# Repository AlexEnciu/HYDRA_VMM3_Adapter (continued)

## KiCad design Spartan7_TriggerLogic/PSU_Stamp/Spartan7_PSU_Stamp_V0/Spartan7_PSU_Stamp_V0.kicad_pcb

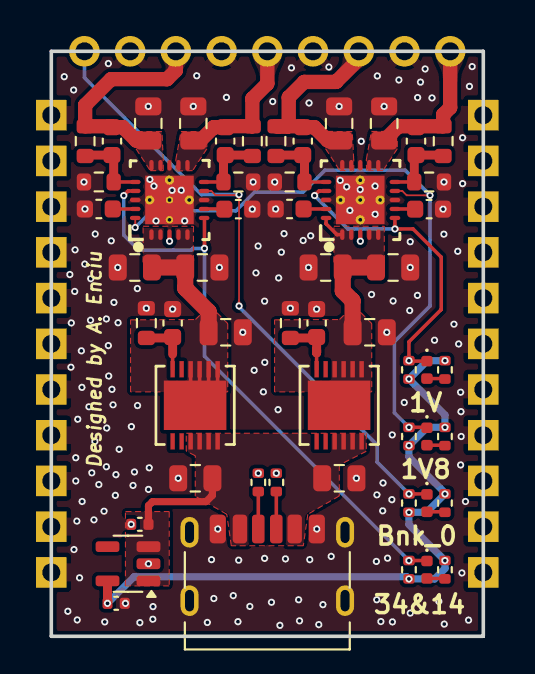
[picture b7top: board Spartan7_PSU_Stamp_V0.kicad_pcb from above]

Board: 4 copper layers, 24.0 x 32.5 mm, 77 parts (0 on the bottom side), 29 nets.

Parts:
C1, C3, C4, C6, C11, C12, C13, C14, C19, C20, C21, C22: 10uF; C_0805_2012Metric
C2, C5: 10p; C_0603_1608Metric
C7, C8, C9, C10: 100nF; C_0603_1608Metric
C15, C16, C17, C18: 10nF; C_0603_1608Metric
C23, C24: 1u; C_0402_1005Metric
D1, D2, D3, D4: 1V_ok; LED_0402_1005Metric
J1: USB4125-GF-A; USB_C_Receptacle_HRO_TYPE-C-31-M-17
J2: Castellated_holes; PinHeader_1x09_P2.54mm_Vertical
J7, J8, J9, J10, J11, J12, J13, J14, J15, J16, J17, J18, J19, J20, J21, J22, J23, J24, J25, J26, J27, J28: Conn_01x01_Pin; PinHeader_1x01_P2.54mm_Vertical
R1, R2: 40k; R_0603_1608Metric
R3, R4: R_3; R_0603_1608Metric
R5, R6: R_4; R_0603_1608Metric
R7, R9: R_1; R_0603_1608Metric
R8, R10: R_2; R_0603_1608Metric
R11, R14, R16, R18: 10k; R_0402_1005Metric
R12, R13, R15, R17: 680; R_0402_1005Metric
R19, R20: 5k1; R_0402_1005Metric
U1, U2: LT3081EDF-TRPBF; DFN-12_DF_LIT-M
U3, U4: TPS7A8801RTJT; RTJ0020D
U5: TPS7A2033; SOT-23-5

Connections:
+3V3: C24.1, R11.1, R12.1, R13.1, R14.1, R15.1, R16.1, R17.1, R18.1, U5.5 (Out)
+5V: C1.1, C4.1, C23.1, J1.A9 (VBUS), J1.B9 (VBUS), U1.9 (IN), U1.10 (IN), U1.11 (IN), U1.12 (IN), U2.9 (IN), U2.10 (IN), U2.11 (IN), U2.12 (IN), U5.1 (In), U5.3 (EN)
/2V5: C3.1, C11.1, C13.1, U1.1 (OUT), U1.2 (OUT), U1.3 (OUT), U1.4 (OUT), U1.13 (OUT), U3.1 (IN1), U3.2 (IN1), U3.4 (IN2), U3.5 (IN2), U3.20 (EN1)
/3V6: C6.1, C12.1, C14.1, U2.1 (OUT), U2.2 (OUT), U2.3 (OUT), U2.4 (OUT), U2.13 (OUT), U4.1 (IN1), U4.2 (IN1), U4.4 (IN2), U4.5 (IN2)
/DONE_0: D4.1 (K), J2.1, R18.2, U4.9 (PG2)
/PG_1V8_ok: D2.1 (K), R14.2, U3.9 (PG2), U4.20 (EN1)
/PG_1V_ok: D1.1 (K), R11.2, U3.6 (EN2), U3.17 (PG1)
/PG_3V3_14_ok: D3.1 (K), R16.2, U4.6 (EN2), U4.17 (PG1)
/V_Bank_14_3V3: C16.1, C22.1, J2.3, R9.1, U4.14 (OUT1), U4.15 (OUT1)
/V_Bank_34_3V3: C18.1, C20.1, J2.5, R4.1, U4.11 (OUT2), U4.12 (OUT2)
/V_aux_1V8: C17.1, C19.1, J2.9, R3.1, U3.11 (OUT2), U3.12 (OUT2)
/V_core_1V: C15.1, C21.1, J2.7, R7.1, U3.14 (OUT1), U3.15 (OUT1)
GND: C1.2, C2.2, C3.2, C4.2, C5.2, C6.2, C7.2, C8.2, C9.2, C10.2, C11.2, C12.2, C13.2, C14.2, C19.2, C20.2, C21.2, C22.2, C23.2, C24.2, J1.A12 (GND), J1.B12 (GND), J1.S1 (SHIELD), J2.2, J2.4, J2.6, J2.8, J7.1, J8.1, J9.1, J10.1, J11.1, J12.1, J13.1, J14.1, J15.1, J16.1, J17.1, J18.1, J19.1, J20.1, J21.1, J22.1, J23.1, J24.1, J25.1, J26.1, J27.1, J28.1, R1.2, R2.2, R5.2, R6.2, R8.2, R10.2, R19.2, R20.2, U3.3 (AGND), U3.8 (SS_CTRL2), U3.13 (AGND), U3.18 (SS_CTRL1), U3.21 (PAD), U4.3 (AGND), U4.8 (SS_CTRL2), U4.13 (AGND), U4.18 (SS_CTRL1), U4.21 (PAD), U5.2 (GND)
unnamed: D1.2 (A), R12.2
unnamed: D2.2 (A), R13.2
unnamed: D3.2 (A), R15.2
unnamed: D4.2 (A), R17.2
unnamed: J1.A5 (CC1), R20.1
unnamed: J1.B5 (CC2), R19.1
unnamed: C2.1, R1.1, U1.6 (SET)
unnamed: C5.1, R2.1, U2.6 (SET)
unnamed: C15.2, R7.2, R8.1, U3.16 (FB1)
unnamed: C17.2, R3.2, R5.1, U3.10 (FB2)
unnamed: C7.1, U3.19 (NR_SS1)
unnamed: C9.1, U3.7 (NR_SS2)
unnamed: C16.2, R9.2, R10.1, U4.16 (FB1)
unnamed: C18.2, R4.2, R6.1, U4.10 (FB2)
unnamed: C8.1, U4.19 (NR_SS1)
unnamed: C10.1, U4.7 (NR_SS2)

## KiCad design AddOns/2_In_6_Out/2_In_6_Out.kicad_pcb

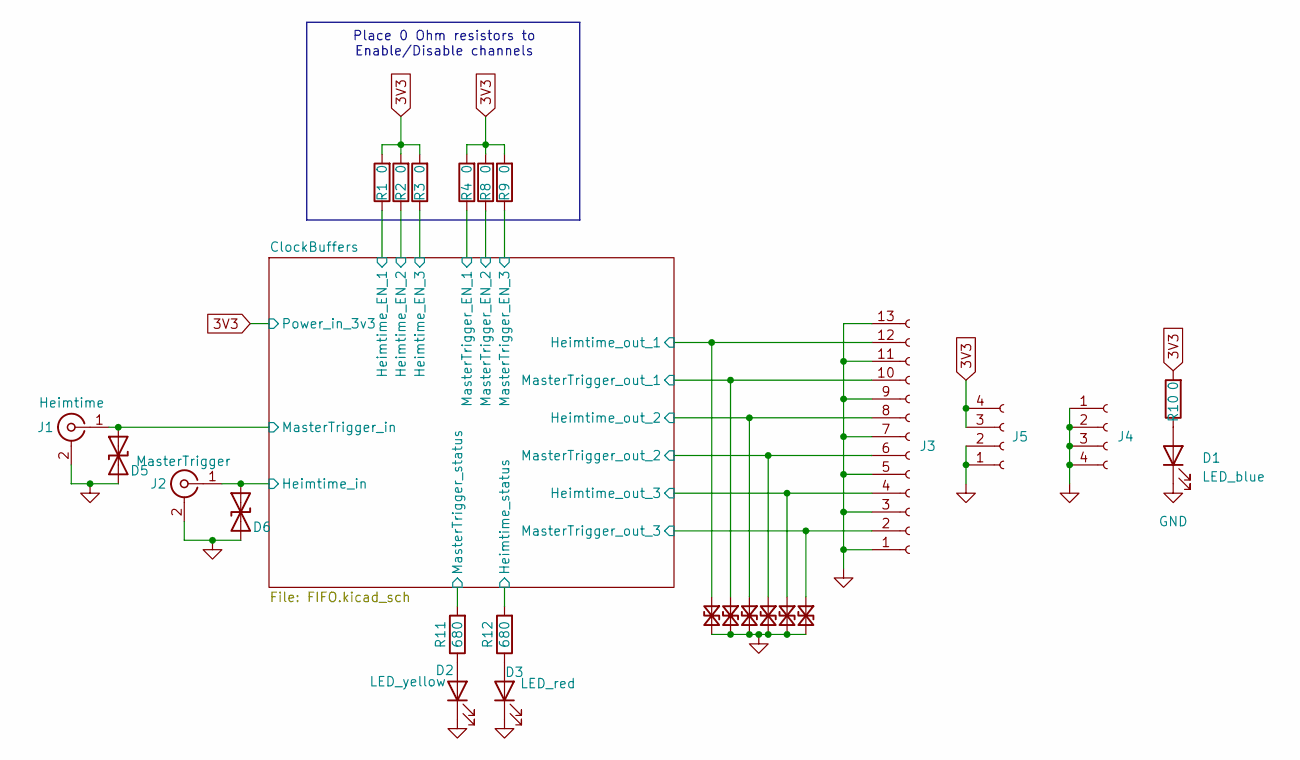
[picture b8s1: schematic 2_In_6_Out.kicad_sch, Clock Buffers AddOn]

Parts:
D1: LED_blue; LED_0603_1608Metric
D2: LED_yellow; LED_0603_1608Metric
D3: LED_red; LED_0603_1608Metric
D5, D6, D7, D8, D9, D10, D11, D13: SP1333-01UTG; D_0201_0603Metric
J1: Heimtime; SAMTEC_MCX-J-P-X-RA-SM1
J2: MasterTrigger; SAMTEC_MCX-J-P-X-RA-SM1
J3: Conn_01x13_Socket; PinHeader_1x13_P1.27mm_Vertical
J4, J5: Conn_01x04_Socket; PinHeader_1x04_P1.27mm_Vertical
R1, R2, R3, R4, R8, R9: 0; R_0402_1005Metric
R10: 0; R_0603_1608Metric
R11, R12: 680; R_0402_1005Metric

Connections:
3V3: J5.3, J5.4, R1.2, R2.2, R3.2, R4.2, R8.2, R9.2, R10.2; also elsewhere on the board
/ClockBuffers/Heimtime_EN_1: R1.1; also elsewhere on the board
/ClockBuffers/Heimtime_EN_2: R2.1; also elsewhere on the board
/ClockBuffers/Heimtime_EN_3: R3.1; also elsewhere on the board
/ClockBuffers/Heimtime_in: D6.1 (A1), J2.1 (In); also elsewhere on the board
/ClockBuffers/Heimtime_out_1: D13.1 (A1), J3.12; also elsewhere on the board
/ClockBuffers/Heimtime_out_2: D8.1 (A1), J3.8; also elsewhere on the board
/ClockBuffers/Heimtime_out_3: D10.1 (A1), J3.4; also elsewhere on the board
/ClockBuffers/Heimtime_status: R12.2; also elsewhere on the board
/ClockBuffers/MasterTrigger_EN_1: R4.1; also elsewhere on the board
/ClockBuffers/MasterTrigger_EN_2: R8.1; also elsewhere on the board
/ClockBuffers/MasterTrigger_EN_3: R9.1; also elsewhere on the board
/ClockBuffers/MasterTrigger_in: D5.1 (A1), J1.1 (In); also elsewhere on the board
/ClockBuffers/MasterTrigger_out_1: D7.1 (A1), J3.10; also elsewhere on the board
/ClockBuffers/MasterTrigger_out_2: D9.1 (A1), J3.6; also elsewhere on the board
/ClockBuffers/MasterTrigger_out_3: D11.1 (A1), J3.2; also elsewhere on the board
/ClockBuffers/MasterTrigger_status: R11.2; also elsewhere on the board
GND: D1.1 (K), D2.1 (K), D3.1 (K), D5.2 (A2), D6.2 (A2), D7.2 (A2), D8.2 (A2), D9.2 (A2), D10.2 (A2), D11.2 (A2), D13.2 (A2), J1.2 (Ext), J2.2 (Ext), J3.1, J3.3, J3.5, J3.7, J3.9, J3.11, J3.13, J4.1, J4.2, J4.3, J4.4, J5.1, J5.2; also elsewhere on the board
unnamed: D1.2 (A), R10.1
unnamed: D2.2 (A), R11.1
unnamed: D3.2 (A), R12.1

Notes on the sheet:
Place 0 Ohm resistors to Enable/Disable channels

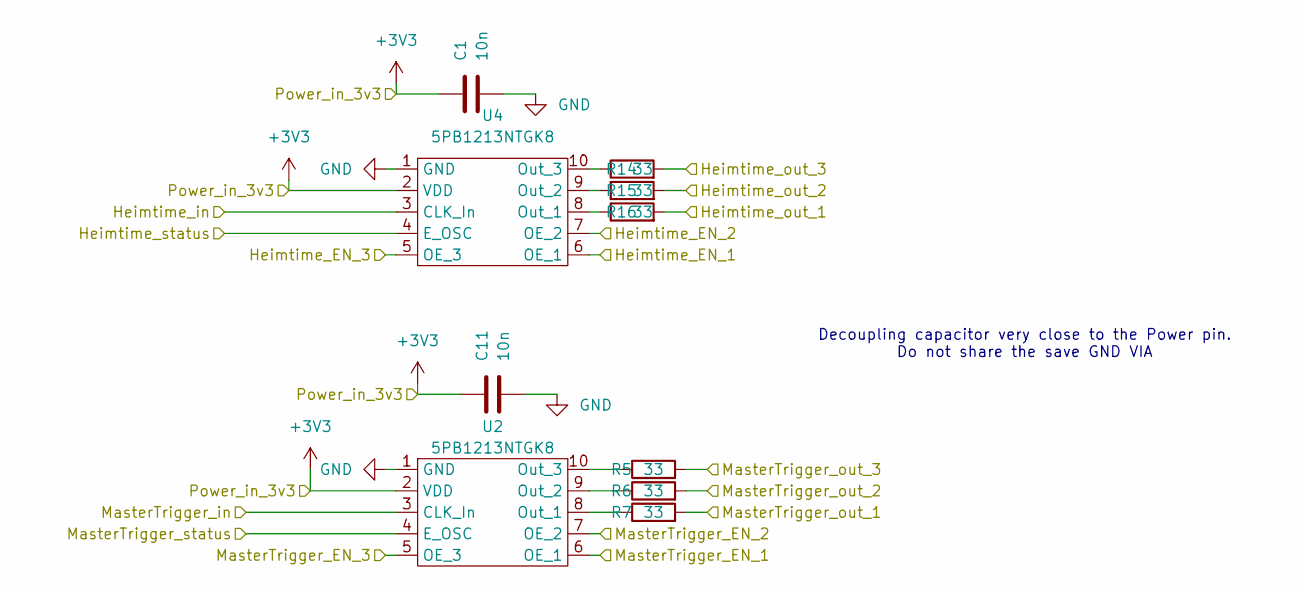
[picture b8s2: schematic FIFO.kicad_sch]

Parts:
C1, C11: 10n; C_0402_1005Metric
R5, R6, R7, R14, R15, R16: 33; R_0402_1005Metric
U2, U4: 5PB1213NTGK8

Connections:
3V3: C1.1, C11.1, U2.2 (VDD), U4.2 (VDD); also elsewhere on the board
/ClockBuffers/Heimtime_EN_1: U4.6 (OE_1); also elsewhere on the board
/ClockBuffers/Heimtime_EN_2: U4.7 (OE_2); also elsewhere on the board
/ClockBuffers/Heimtime_EN_3: U4.5 (OE_3); also elsewhere on the board
/ClockBuffers/Heimtime_in: U4.3 (CLK_In); also elsewhere on the board
/ClockBuffers/Heimtime_out_1: R16.2; also elsewhere on the board
/ClockBuffers/Heimtime_out_2: R15.2; also elsewhere on the board
/ClockBuffers/Heimtime_out_3: R14.2; also elsewhere on the board
/ClockBuffers/Heimtime_status: U4.4 (E_OSC); also elsewhere on the board
/ClockBuffers/MasterTrigger_EN_1: U2.6 (OE_1); also elsewhere on the board
/ClockBuffers/MasterTrigger_EN_2: U2.7 (OE_2); also elsewhere on the board
/ClockBuffers/MasterTrigger_EN_3: U2.5 (OE_3); also elsewhere on the board
/ClockBuffers/MasterTrigger_in: U2.3 (CLK_In); also elsewhere on the board
/ClockBuffers/MasterTrigger_out_1: R7.2; also elsewhere on the board
/ClockBuffers/MasterTrigger_out_2: R6.2; also elsewhere on the board
/ClockBuffers/MasterTrigger_out_3: R5.2; also elsewhere on the board
/ClockBuffers/MasterTrigger_status: U2.4 (E_OSC); also elsewhere on the board
GND: C1.2, C11.2, U2.1 (GND), U4.1 (GND); also elsewhere on the board
unnamed: R7.1, U2.8 (Out_1)
unnamed: R6.1, U2.9 (Out_2)
unnamed: R5.1, U2.10 (Out_3)
unnamed: R16.1, U4.8 (Out_1)
unnamed: R15.1, U4.9 (Out_2)
unnamed: R14.1, U4.10 (Out_3)

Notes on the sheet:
Decoupling capacitor very close to the Power pin. Do not share the save GND VIA

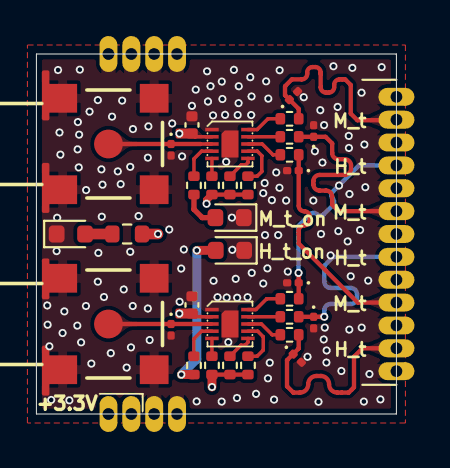
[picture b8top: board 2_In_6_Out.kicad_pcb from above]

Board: 4 copper layers, 20.0 x 20.0 mm, 35 parts (0 on the bottom side), 27 nets.

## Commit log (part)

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2025-07-14 Adjust C7 footprint position on PSU Stamp PCB
    Moved the C7 capacitor footprint to new coordinates (138.38, 74.27) on the Spartan7_PSU_Stamp_V0.kicad_pcb file for improved layout. Updated backup ZIP to reflect latest PCB changes.
2025-07-15 Add USB-C power and TPS7A2033PDBVR symbol
    Added USB_C_Power schematic, new TPS7A2033PDBVR symbol and library, and updated net names and layout for improved clarity. Also included new backup files and made minor footprint and netlist adjustme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
2025-07-15 Update net assignments and add vias in KiCad PCB
    Reassigned several net numbers and names in Spartan7_PSU_Stamp_V0.kicad_pcb for improved clarity and consistency. Added multiple via definitions and updated related PCB segments. Removed old backup f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
2025-07-16 Add status LEDs and update power nets
    Added new 0402 LEDs (D1, D4) and supporting resistor (R12) for power-good status indication. Updated net assignments and replaced a capacitor footprint with an LED. Modified schematic and PCB files t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
2025-07-16 Update PCB netlist and add GND test point
    Renumbered and cleaned up net assignments in the KiCad PCB file, updated several resistor values, and added a new GND test point (J4). Also updated backup and plot files to reflect the latest schemat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
2025-07-16 Add pin header footprints and update PCB layout
    Replaced C14 footprint with a pin header (J10), added new pin headers J11 and J25, and updated the PCB layout parameters. Also swapped C13 and C14 positions and made related changes to the BOM and ba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
2025-08-01 Add initial Spartan7 TriggerController PCB files
    Added KiCad project files, schematic, PCB layout, symbol and footprint libraries, backup archives, and supporting documentation for the Spartan7 TriggerController. This commit establishes the base ha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
2025-08-07 Update PCB layout and net assignments for new capacitors
    Added new nets and updated net assignments for several capacitors (C11, C12, C13, C14, C18, C19, C20, C21) in the PCB layout. Modified footprints, positions, and values for various components includi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
2025-08-07 Add stiffener models and update PCB stackup/materials
    Added STEP and SLDPRT models for 4-pin and 17-pin stiffeners and referenced them in the PCB layout. Updated stackup layers with material, epsilon_r, and loss_tangent properties. Removed obsolete tear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
2025-08-19 Update PCB layout and add new backup and SPICE files
    Added new backup ZIP files and SPICE simulation files for Clock_Buffers_1-16 and HYDRA_VMM3_CARD_V3_Flex, while removing outdated backup files. Updated multiple footprints and component placements in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
2026-02-08 Convert LED to SMD; adjust stackup & silk
    Update PCB layout: replace through-hole LED footprint with an LED_SMD 0603 footprint (pads converted to SMD roundrect, 3D model updated), adjust footprint positions/orientations and text/font sizes. 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
2026-03-23 new flex pcb BOM
